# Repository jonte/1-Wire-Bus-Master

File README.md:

1-Wire Bus Master
=================

These are KiCad schematics and project files for a 1-Wire Bus Master module,
capable of mastering 8 1-Wire busses.

This module is meant to be connected to, and driven by, a host uC, such as a Raspberry Pi or an Arduino. The host uC must be capable of I2C communication.

The module is powered by the Maxim DS2482 1-Wire bus master chip.

Features
--------

- Break-out of 8 1-Wire busses from the DS2482
- Screw terminal connectors for host and all 8 busses
- 4.5cm x 4cm footprint
- 4 x 3.4mm mounting holes (M3 clearance hole size)
- Optional pull-up resistors for SDA and SCL (toggled via jumpers)

Notes for Raspberry Pi
----------------------

The Raspberry Pi has internal pull-ups for I2C, so the J1 and J2 jumpers should not be populated when using a Raspberry Pi.

The I2C bus must be enabled to communicate with the board, this can be done using `raspi-config`, in the `Interfacing Options -> I2C` menu.

The ds2482 kernel module, included in the mainline kernels, is compatible with this board and can be used as follows:

    modprobe ds2482
    echo ds2482 0x18 > /sys/bus/i2c/devices/i2c-1/new_device

A systemd service file for Raspberry Pi is available in `systemd/ds2482.service`.

In the above example, `0x18` is the board's I2C address. This will remain valid as long as the `AD0-2` pins are connected to ground. If you change this, you will also have to change the board I2C address.

The bus master devices, and any connected 1-Wire devices will appear under `/sys/bus/w1/devices/`.

3D Rendering
------------

License
-------

This project is licensed under the CERN Open Hardware Licence v1.2.

See LICENSE.txt

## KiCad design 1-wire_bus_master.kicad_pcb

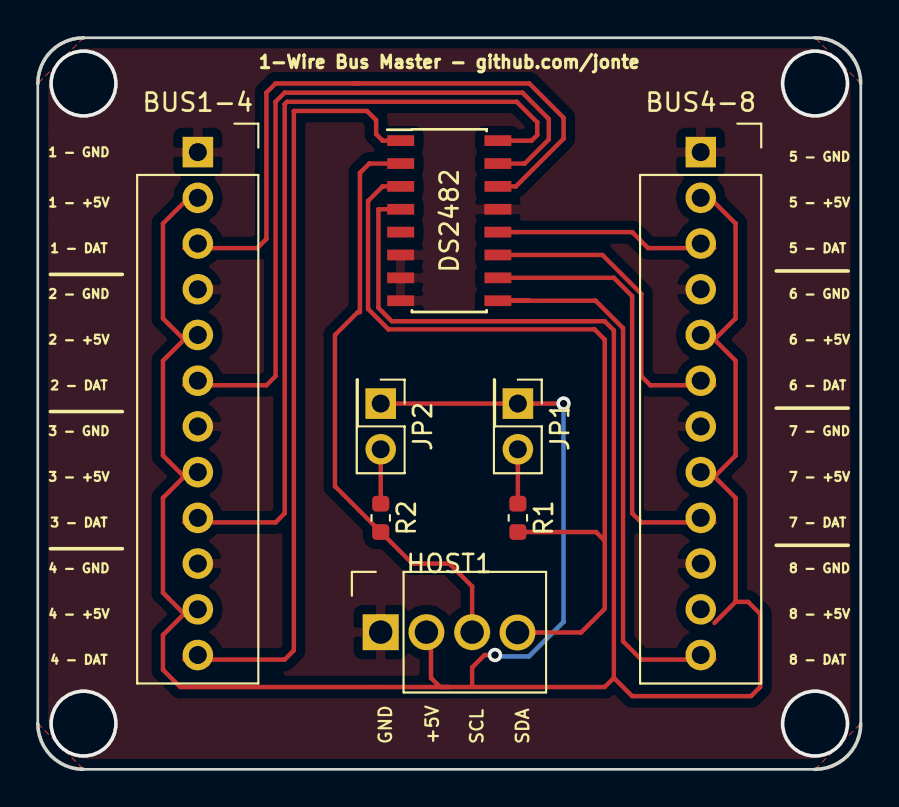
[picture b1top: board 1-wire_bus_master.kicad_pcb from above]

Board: 2 copper layers, 45.7 x 40.6 mm, 8 parts (0 on the bottom side), 14 nets.

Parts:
BUS1-4, BUS4-8: Conn_01x12; OSTVN12A150
DS2482: DS2482-800; SOIC-16_3.9x9.9mm_P1.27mm
HOST1: Conn_01x04; OSTVN04A150
JP1: JMP_PU_SDA; PinHeader_2x01_P2.54mm_Vertical
JP2: JMP_PU_SCL; PinHeader_2x01_P2.54mm_Vertical
R1, R2: 1k7; R_0603_1608Metric

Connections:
+5V: BUS1-4.2, BUS1-4.5, BUS1-4.8, BUS1-4.11, BUS4-8.2, BUS4-8.5, BUS4-8.8, BUS4-8.11, DS2482.4, HOST1.2, JP1.1, JP2.1
/BUS1: BUS1-4.3, DS2482.14
/BUS2: BUS1-4.6, DS2482.15
/BUS3: BUS1-4.9, DS2482.16
/BUS4: BUS1-4.12, DS2482.1
/BUS5: BUS4-8.3, DS2482.12
/BUS6: BUS4-8.6, DS2482.11
/BUS7: BUS4-8.9, DS2482.10
/BUS8: BUS4-8.12, DS2482.9
GND: BUS1-4.1, BUS1-4.4, BUS1-4.7, BUS1-4.10, BUS4-8.1, BUS4-8.4, BUS4-8.7, BUS4-8.10, DS2482.6, DS2482.7, DS2482.8, DS2482.13, HOST1.1
unnamed: DS2482.2, HOST1.3, R2.2
unnamed: DS2482.3, HOST1.4, R1.2
unnamed: JP1.2, R1.1
unnamed: JP2.2, R2.1

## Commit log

2019-09-07 Initial commit
    This adds the first revision of the board, as it looks when sent to the
    first round of manufacturing.
2019-09-19 Make SDA & SCL pull-ups optional, document Pi usage
2019-09-19 Add systemd service file for kernel module
